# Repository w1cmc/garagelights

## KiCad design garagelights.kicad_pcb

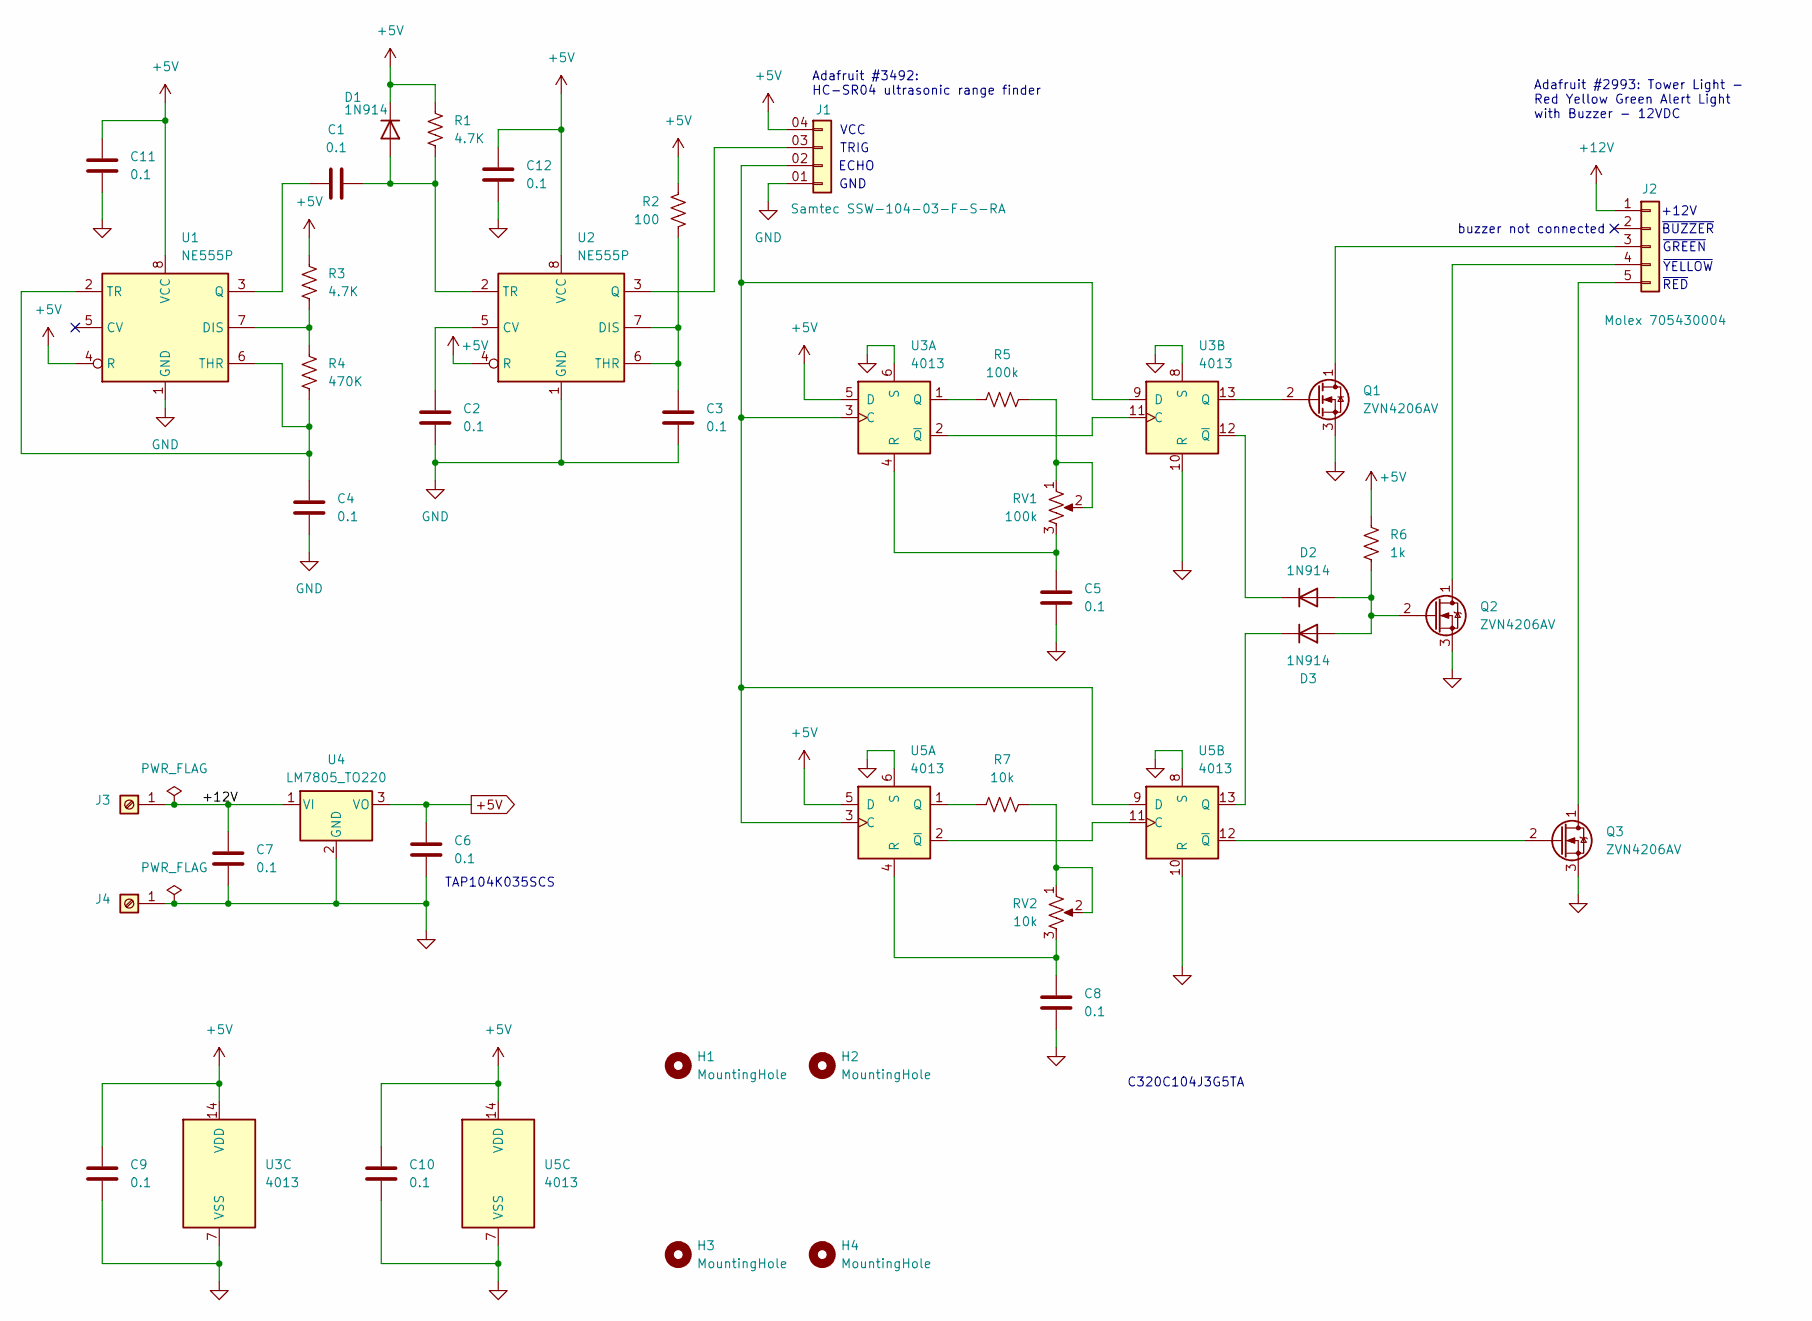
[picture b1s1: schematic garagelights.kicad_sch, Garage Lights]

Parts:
C1, C2, C3, C4, C5, C6, C7, C8, C9, C10, C11, C12: 0.1; C_Disc_D5.0mm_W2.5mm_P2.50mm
D1, D2, D3: 1N914; D_DO-35_SOD27_P7.62mm_Horizontal
H1, H2, H3, H4: MountingHole; MountingHole_3.2mm_M3
J1: Samtec SSW-104-03-F-S-RA; SAMTEC_SSW-104-03-F-S-RA
J2: Molex 705430004; CONN_SDA-70543-xxxx_05_MOL
J3, J4: Screw_Terminal_01x01; KEYSTONE_8191
Q1, Q2, Q3: ZVN4206AV; TO-92S
R1, R3: 4.7K; R_Axial_DIN0207_L6.3mm_D2.5mm_P10.16mm_Horizontal
R2: 100; R_Axial_DIN0207_L6.3mm_D2.5mm_P10.16mm_Horizontal
R4: 470K; R_Axial_DIN0207_L6.3mm_D2.5mm_P10.16mm_Horizontal
R5: 100k; R_Axial_DIN0207_L6.3mm_D2.5mm_P10.16mm_Horizontal
R6: 1k; R_Axial_DIN0207_L6.3mm_D2.5mm_P10.16mm_Horizontal
R7: 10k; R_Axial_DIN0207_L6.3mm_D2.5mm_P10.16mm_Horizontal
RV1: 100k; POT_3386F
RV2: 10k; POT_3386F
U1, U2: NE555P; DIP-8_W7.62mm_Socket
U3, U5: 4013; DIP-14_W7.62mm_Socket
U4: LM7805_TO220; TO-220-3_Vertical

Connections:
+5V: C6.1, C9.1, C10.1, C11.1, C12.1, D1.1 (K), J1.04 (Pin_1), R1.1, R2.1, R3.1, R6.1, U1.4 (R), U1.8 (VCC), U2.4 (R), U2.8 (VCC), U3.5 (D), U3.14 (VDD), U4.3 (VO), U5.5 (D), U5.14 (VDD)
+12V: C7.1, J2.1, J3.1 (Pin_1_1), U4.1 (VI)
GND: C2.2, C3.2, C4.2, C5.2, C6.2, C7.2, C8.2, C9.2, C10.2, C11.2, C12.2, J1.01 (Pin_4), J4.1 (Pin_1_1), Q1.3 (S), Q2.3 (S), Q3.3 (S), U1.1 (GND), U2.1 (GND), U3.6 (S), U3.7 (VSS), U3.8 (S), U3.10 (R), U4.2 (GND), U5.6 (S), U5.7 (VSS), U5.8 (S), U5.10 (R)
unnamed: C1.2, D1.2 (A), R1.2, U2.2 (TR)
unnamed: D2.2 (A), D3.2 (A), Q2.2 (G), R6.2
unnamed: D2.1 (K), U3.12 (~Q)
unnamed: D3.1 (K), U5.13 (Q)
unnamed: J1.03 (Pin_2), U2.3 (Q)
unnamed: J1.02 (Pin_3), U3.3 (C), U3.9 (D), U5.3 (C), U5.9 (D)
unnamed: J2.3, Q1.1 (D)
unnamed: J2.4, Q2.1 (D)
unnamed: J2.5, Q3.1 (D)
unnamed: Q1.2 (G), U3.13 (Q)
unnamed: Q3.2 (G), U5.12 (~Q)
unnamed: R5.2, RV1.1, RV1.2
unnamed: R7.2, RV2.1, RV2.2
unnamed: R3.2, R4.1, U1.7 (DIS)
unnamed: C1.1, U1.3 (Q)
unnamed: C4.1, R4.2, U1.2 (TR), U1.6 (THR)
unnamed: C2.1, U2.5 (CV)
unnamed: C3.1, R2.2, U2.6 (THR), U2.7 (DIS)
unnamed: R5.1, U3.1 (Q)
unnamed: C5.1, RV1.3, U3.4 (R)
unnamed: U3.2 (~Q), U3.11 (C)
unnamed: R7.1, U5.1 (Q)
unnamed: C8.1, RV2.3, U5.4 (R)
unnamed: U5.2 (~Q), U5.11 (C)

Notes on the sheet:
Adafruit #3492: HC-SR04 ultrasonic range finder
~{GREEN}
TAP104K035SCS
VCC
ECHO
Adafruit #2993: Tower Light - Red Yellow Green Alert Light with Buzzer - 12VDC
GND
buzzer not connected
~{BUZZER}
+12V
TRIG
~{YELLOW}
~{RED}
C320C104J3G5TA

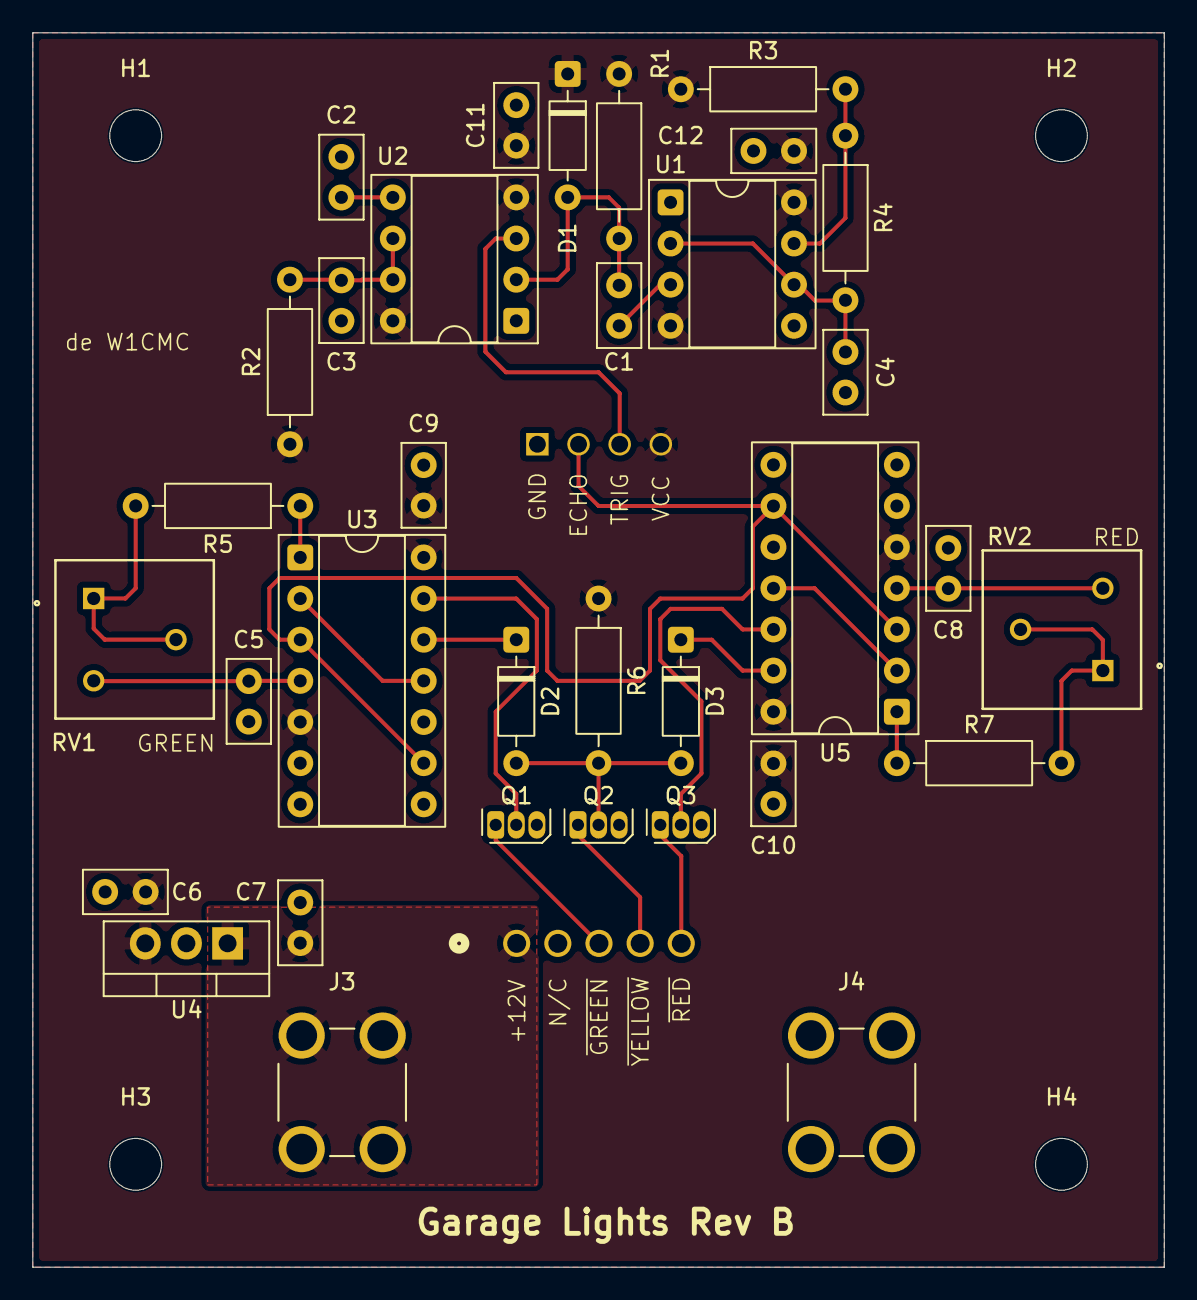
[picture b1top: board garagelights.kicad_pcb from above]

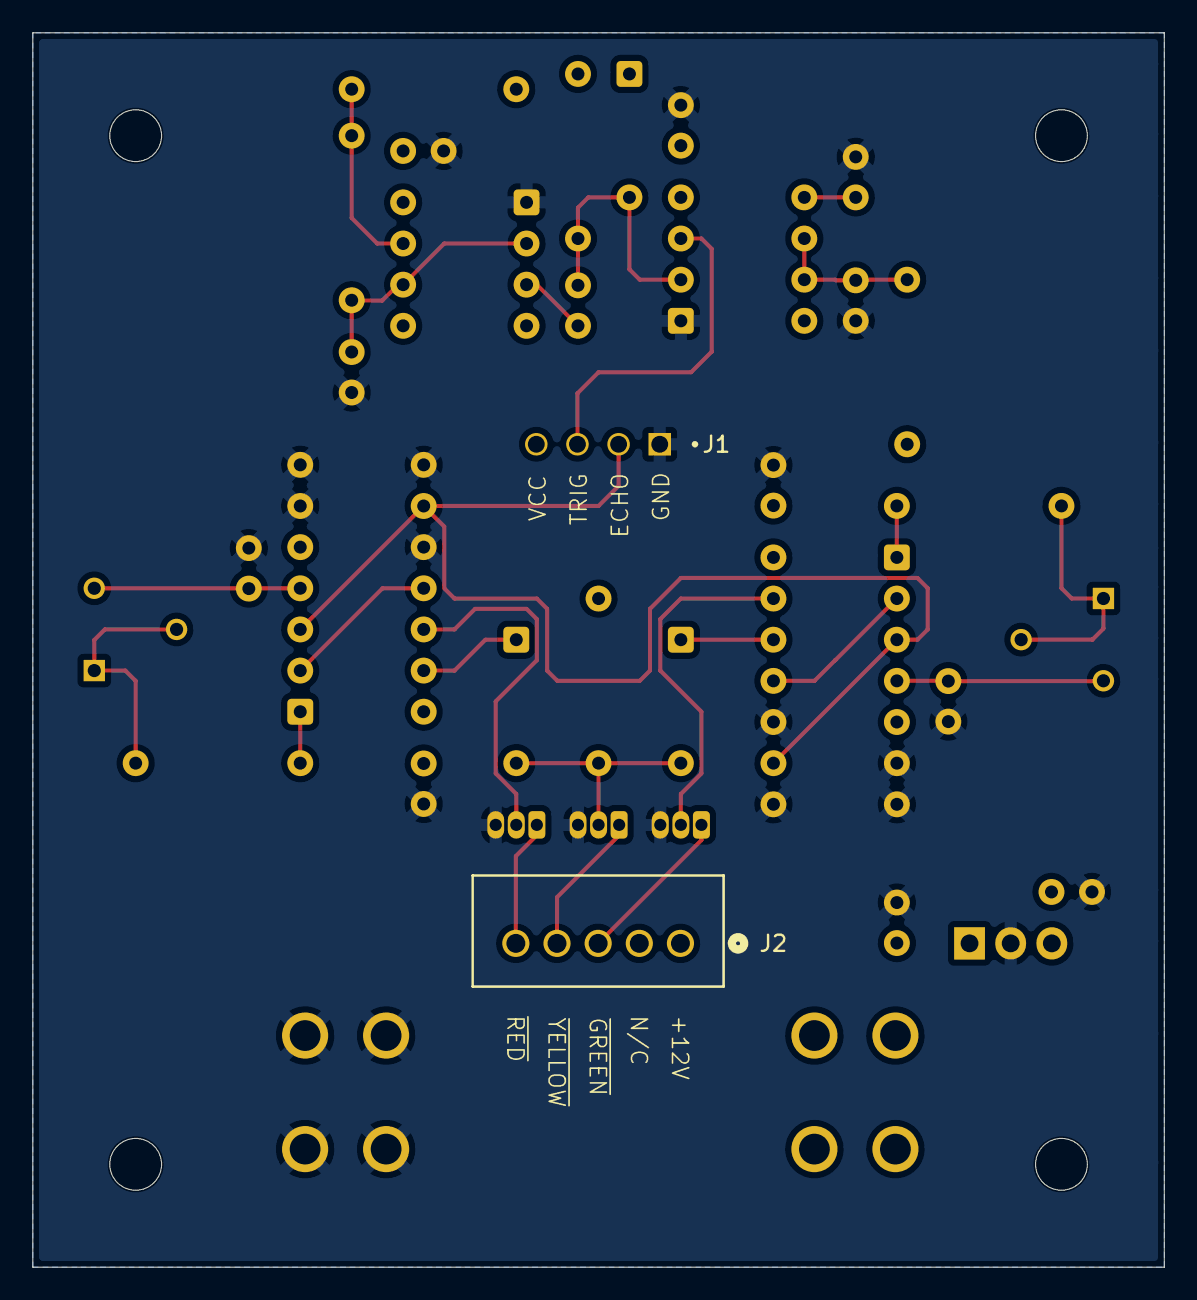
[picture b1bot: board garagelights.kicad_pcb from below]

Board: 2 copper layers, 69.8 x 76.2 mm, 40 parts (2 on the bottom side), 27 nets.

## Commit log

2025-11-02 First working prototype
2025-11-03 Added FETs and yellow light
2025-11-11 Working towards debouncing.
2025-12-02 More hierarchical; adding debounce
2025-12-05 prettify
2026-04-08 mostly finished layout
2026-04-09 Added screw terminals and mounting holes
    Also working towards reducing the number of layers to two.
2026-04-09 Kinda sorta Rev_A
    Finished the layout and brought it down to two layers, one of which
    is a ground plane. Imported missing 3D models.
2026-04-09 started mechanical design
2026-04-10 Moved the connectors to the bottom side
    Makes the mechanical design easier. Also some tweaks to reduce
    inductance on the +5V net.
2026-04-10 Change "PING" to "TRIG" to better match HC-SR04 nomenclature.
2026-04-10 Spec Samtec connectors for the socket headers.
    Also more fussing with position and text.
2026-04-10 Put the mounting holes into the schematic.
    So that we don't keep losing them when we update the layout from
    the schematic.
2026-04-10 Rev A: as submitted to Osh Park order #fmnAZ4b4
2026-04-10 churn
2026-04-11 Added a PWR_FLG and exclusion to clear ERCs
2026-04-13 Added plot output directory for schematics
2026-04-13 Added LTSpice simulation of the clocking circuit
2026-04-13 git-ignore FreeCAD backups
2026-04-13 git-ignore KiCAD cache and backups
2026-04-15 Changed the timing capacitors: 1 uF ceramic C0G isn't a thing.
2026-04-26 Update to KiCAD 10.0, replace J2 with 5-pin
    J2 was 6-pin, but the ground pin was superfluous. The light tower
    is switched on the low side, so there is no ground conductor.
2026-04-26 Fixed a couple of boo-boos:
    1. Bigger resistors
    2. Correct footprint for pots
2026-04-27 Outputs for Rev B
2026-04-28 More mechanical work, bump the revision letter on the Schematic
    Mostly done with mechanical holes and pockets.
2026-04-28 should have been part of the previous commit
2026-04-28 Ignore history and be doomed to repeat it.
2026-05-04 Added power entry and switch
2026-05-05 Added HC-SR04 model to the mechanical design.
2026-05-05 Added BoM
2026-05-05 more churn; made changes and then unmade them
2026-05-06 added sonar holder
2026-05-07 Exported STEP file for sonar holder
2026-05-07 Refinements to sonar holder
    The constraints are better: a single value sets the clearance
    around the HC-SR04 PCB.
2026-05-07 add 3-d print files
2026-05-08 Added long screws through sonar holder.
    And STEP file for short screws.
2026-05-08 Added the short screws.
2026-05-24 Move the power entry mechanicals to a subdirectory.
    Schurter 6100-33.
